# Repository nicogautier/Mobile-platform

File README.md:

# Mobile-platform

## Presentation

The mobile platform robot was developed at the [Robotics Laboratory](https://robolab.si/) of the University of Ljubljana.

The mobile platform is a robot that uses its sensors to identify and move through its environment. The final goal of the platform will be to be used in an indoor environment such as a warehouse or a retail store. It will also be combined with a collaborative manipulator robot for precise handling.

| Product | Description |
| ------ | ------ |
|[SICK nanoScan3](https://www.sick.com/hk/en/safety-laser-scanners/safety-laser-scanners/nanoscan3/nans3-caaz30an1/p/p653980?ff_data=JmZmX2lkPXA2NTM5ODAmZmZfbWFzdGVySWQ9cDY1Mzk4MCZmZl90aXRsZT1OQU5TMy1DQUFaMzBBTjEmZmZfcXVlcnk9JmZmX3Bvcz0xJmZmX29yaWdQb3M9MSZmZl9wYWdlPTEmZmZfcGFnZVNpemU9MjQmZmZfb3JpZ1BhZ2VTaXplPTI0JmZmX3NpbWk9OTcuMA==)| Laser scanners for platform protection and localization|
|[ Beckhoff CX5140 ](https://www.beckhoff.com/en-us/products/ipc/embedded-pcs/cx5100-intel-atom/cx5140.html)|Embedded PC for low-level control of sensors and actuators|

## Features

| Program | Description |
| ------ | ------ | 
|[TwinCAT](https://www.beckhoff.com/en-en/products/automation/twincat/?pk_campaign=AdWords-AdWordsSearch-TwinCAT_EN&pk_kwd=twincat&gclid=EAIaIQobChMI4qSCndXt9wIVCZBoCR0AcgaeEAAYASAAEgLjsvD_BwE)| supervises low level control of the platform (motors, joystick, laser field security, ... ) |  
|[ROS](https://www.ros.org/)| supervises high level algorithms (path-finding, SLAM algorithm, ... ) |

## How to use it

This section will explain you how to use this project.
**Note:** You will not be able to use these programs as they are if you use another robot (this one is a custom robot created in the lab), but you can of course modify or reuse part of the programs to suit them to your application.   

First you need to get the files from git:
```sh
git clone https://github.com/nicogautier/Mobile-platform && cd Mobile-platform
```

### ROS program

#### platform_communication
The **ADScommunication** node of the platform\_communication package allows to communicate with the TwinCAT program. It receives commands from the **/cmd\_vel** topic and sends them to the PLC. It also publishes the odometry on the **/odom** topic according to the values of the wheel encoders. This will allow you for example to use the ROS [navigation](https://wiki.ros.org/navigation) stack which required communication on these two subjects.

To use it in your program, you can add and compile the platform_communication package in your ROS project. Then add this line to your launch file.  

```sh
<node pkg="platform_communication" type="ADSCommunication" name="ADSCommunication"/>
```

If you want to modify this node, I recommend that you consult the [**ADS Beckhoff**](ADS&#32;Beckhoff/) folder which will explain how to use the ADS library. The two main arrays used to exchange data with the PLC are **"ControlGVL.robot\_odom "** received by ADS notification for odometry and **"ControlGVL.vel\_robot "** to send speed goals.

#### platform_main
The platform\_main package contains the main launch file and the configuration files used to implement ROS [navigation](https://wiki.ros.org/navigation) stack. It uses the [**sick\_safetyscanners**](https://wiki.ros.org/sick_safetyscanners) node to get the laserscan of the two sensors. It also uses [**TEB local planner**](https://wiki.ros.org/teb_local_planner) for the local trajectories and [**rtabmap**](http://wiki.ros.org/rtabmap_ros) for the SLAM algorithm.

#### platform_lift

The **lift_communication.py** node of the package allows to communicate with the SCU control unit through the RS232 serial [**interface**](https://medialibrary.ewellix.com/asset/16222) that manage the lift actuators . It implements a **/moveLift** action server that moves the lift to the desired position and sends a success message when reaching the final position. It also implements a **/posLift** service that returns the position of the lift.

You can add this line to your launch file to use the node. 
```sh
<node pkg="platform_lift" type="lift_communication.py" name="lift_communication"/>
```
You may have to change the port for serial communication which is currently "*/dev/ttyUSB0*" in the init_serial() function of serial_interface.py. 

#### platform_joystick

This package allows the use of a [**Logitech Extreme 3D**](https://www.logitechg.com/fr-fr/products/space/extreme-3d-pro-joystick.942-000031.html) joystick to control the mobile platform. It implements additional features compared to the joystick connected to the Beckhoff controller. You can use the **joystick.launch** file alone:

```sh
roslaunch platform_joystick joystick.launch joystickOnly:="true"
```

or in addition to the **platform_main** launchfile. Note: to enable the use of the joystick you must put the third axis down (up: ros navigation, middle: stop).

#### platform_measurements

This package was used to perform several tests: use of an external setpoint generator in TwinCAT, accuracy of the platform movements, and accuracy of the ROS navigation implementation.  

### TwinCAT program

#### Motors

The **FB_RUN_MOTOR** controls all 4 wheels for holonomic movements. It also implements the TwinCAT external setpoint generator. It can be used by both the joystick and the ROS program. The program retrieves the values from the wheel encoders to calculate the odometry and send it to ROS.

#### Sensors
The **SensorsMain** program manages the communication with the two sensors. It calculates the fields to be applied according to the current direction. It also limits the maximum speed allowed according to the fields of the sensors that are triggered. There are 8 different orientations (see next section).

#### Variables you might want to adjust

For future people who will work on the platform, here are some variables that you will probably have to adapt to your new constraints.

| Name| Type | Description |
|------|------|------|
|ControlGVL.vel_robot| LReal[3]| Velocity command sent by the ROS program.|
|ControlGVL.robot_odom|LReal[6]|Odometry send to the ROS program.|
|FB_RUN_MOTOR.ACC_MAX| LReal| Maximum acceleration allowed for the motors.|
|FB_RUN_MOTOR.VEL_WHEEL_MAX|LReal|Maximum speed allowed for the motors.|
|SensorsMain.VMAX|LReal|Maximum speed allowed for the platform when no safety field is triggered (other maximum speeds are also based on this value.)|
|SensorsMain.VTHMAX|LReal|Maximum permissible rotation speed of the platform when the first safety field is not triggered.|

### SICK sensors security
The objective was to have a safety field around the platform to stop it (cut the power safely) if there is an obstacle very close and representing a danger. 

There are also several sets of directional fields that will stop the platform (software) or reduce the maximum speed of the platform depending on the field triggered. Each set has three warning fields (18 cm, 1 m and 2.5 m). The set of fields used will be adapted according to the direction in which the platform is moving.

Each sensor is connected to the TwinCAT PLC to inform about the triggering of a field and also to the safety module of the platform which will cut the power if necessary.

You will find in the [**safety designer**](safety&#32;designer/) folder the fields used and the sensor configurations. In the [**kicad**](kicad/) folder you will find the PCB diagram used to connect the sensors to the PLC.

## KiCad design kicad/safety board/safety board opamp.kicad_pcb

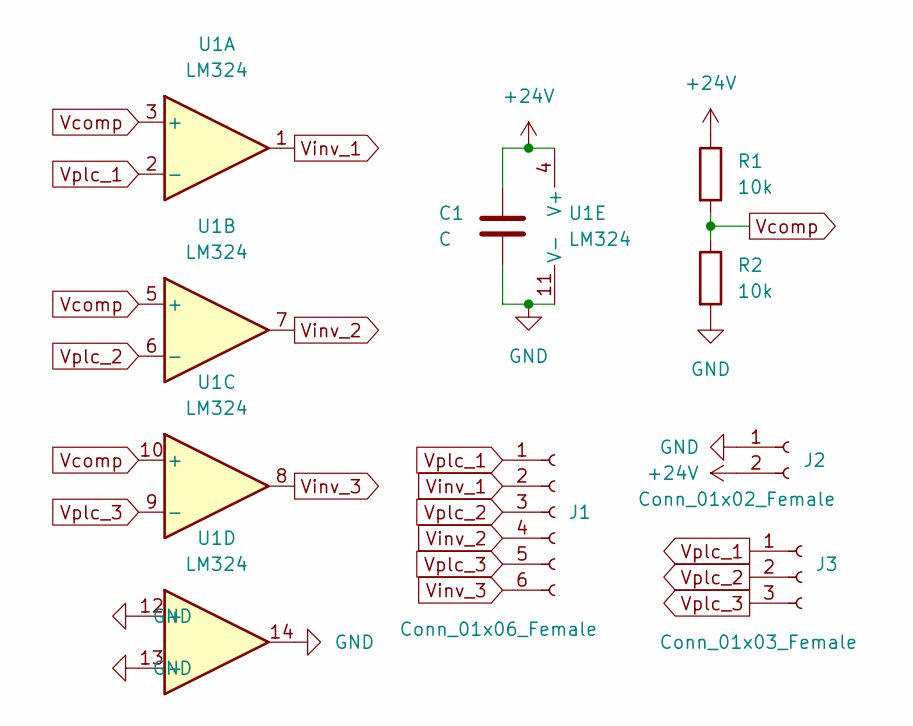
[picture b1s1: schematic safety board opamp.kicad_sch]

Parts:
C1: C
J1: Conn_01x06_Female; PinSocket_1x06_P2.54mm_Vertical
J2: Conn_01x02_Female; PinSocket_1x02_P2.54mm_Vertical
J3: Conn_01x03_Female; PinSocket_1x03_P2.54mm_Vertical
R1, R2: 10k; R_Axial_DIN0207_L6.3mm_D2.5mm_P10.16mm_Horizontal
U1: LM324; DIP-14_W7.62mm_Socket

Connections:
+24V: C1.1, J2.2, R1.1, U1.4 (V+)
GND: C1.2, J2.1, R2.2, U1.11 (V-), U1.12 (+), U1.13 (-), U1.14
Vcomp: R1.2, R2.1, U1.3 (+), U1.5 (+), U1.10 (+)
Vinv_1: J1.2, U1.1
Vinv_2: J1.4, U1.7
Vinv_3: J1.6, U1.8
Vplc_1: J1.1, J3.1, U1.2 (-)
Vplc_2: J1.3, J3.2, U1.6 (-)
Vplc_3: J1.5, J3.3, U1.9 (-)

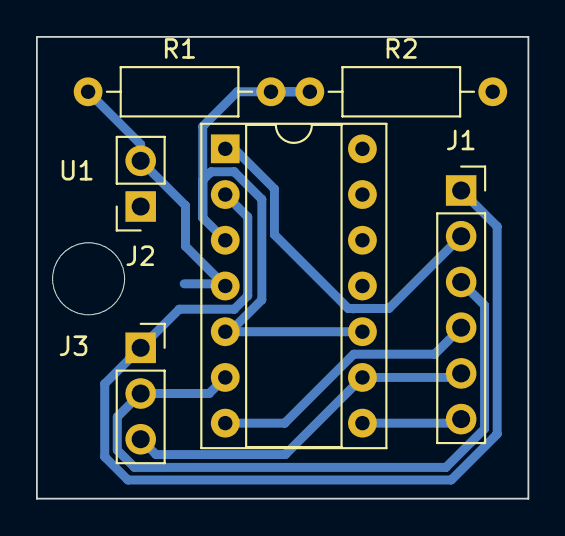
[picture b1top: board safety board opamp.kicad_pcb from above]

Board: 2 copper layers, 27.3 x 25.7 mm, 7 parts (1 on the bottom side), 9 nets.

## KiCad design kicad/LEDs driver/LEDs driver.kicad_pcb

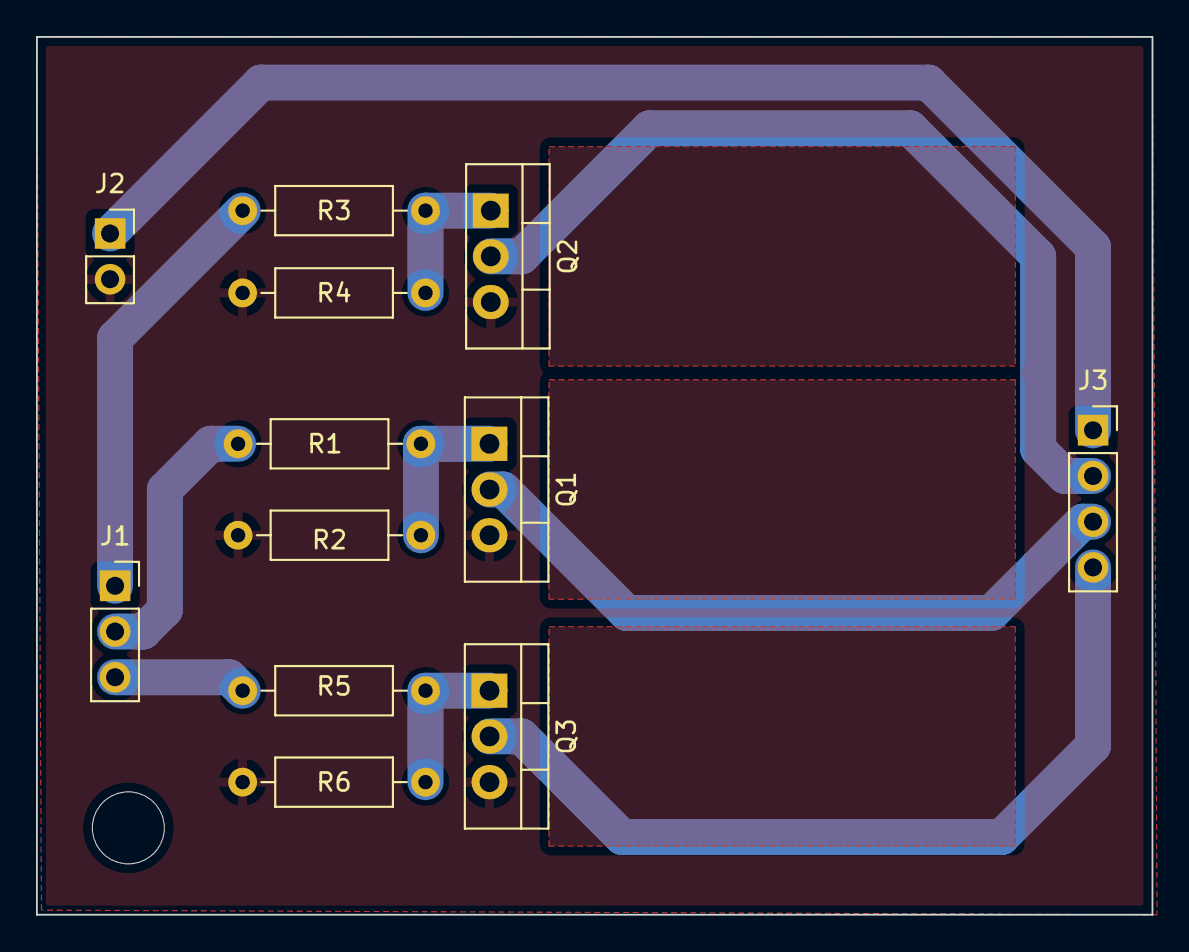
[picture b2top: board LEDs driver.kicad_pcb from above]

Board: 2 copper layers, 62.0 x 48.8 mm, 12 parts (0 on the bottom side), 11 nets.

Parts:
J1: Conn_01x03_Female; PinSocket_1x03_P2.54mm_Vertical
J2: Conn_01x02_Female; PinSocket_1x02_P2.54mm_Vertical
J3: Conn_01x04_Female; PinSocket_1x04_P2.54mm_Vertical
Q1, Q2, Q3: BUZ11; TO-220-3_Vertical
R1, R2, R3, R4, R5, R6: R; R_Axial_DIN0207_L6.3mm_D2.5mm_P10.16mm_Horizontal

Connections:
+12V: J2.1, J3.1
Bin: J1.3, R5.1
Bout: J3.4, Q3.2 (D)
GND: J2.2, Q1.3 (S), Q2.3 (S), Q3.3 (S), R2.2, R4.2, R6.2
Gin: J1.1, R3.1
Gout: J3.2, Q2.2 (D)
unnamed: Q1.1 (G), R1.2, R2.1
unnamed: Q2.1 (G), R3.2, R4.1
unnamed: Q3.1 (G), R5.2, R6.1
Rin: J1.2, R1.1
Rout: J3.3, Q1.2 (D)

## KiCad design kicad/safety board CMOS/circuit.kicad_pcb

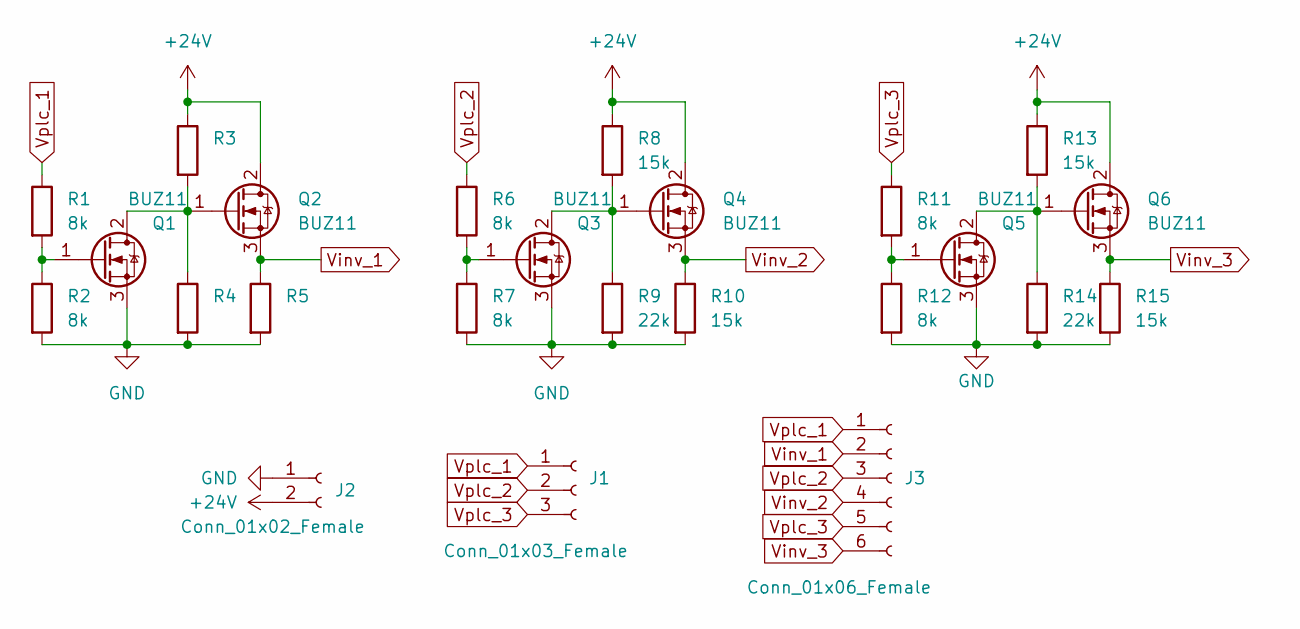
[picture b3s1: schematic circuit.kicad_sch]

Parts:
J1: Conn_01x03_Female; PinSocket_1x03_P2.54mm_Vertical
J2: Conn_01x02_Female; PinSocket_1x02_P2.54mm_Vertical
J3: Conn_01x06_Female; PinSocket_1x06_P2.54mm_Vertical
Q1, Q2, Q3, Q4, Q5, Q6: BUZ11; TO-220-3_Vertical
R1, R2, R6, R7, R11, R12: 8k; R_Axial_DIN0207_L6.3mm_D2.5mm_P10.16mm_Horizontal
R3, R4, R5: R_Axial_DIN0207_L6.3mm_D2.5mm_P10.16mm_Horizontal
R8, R10, R13, R15: 15k; R_Axial_DIN0207_L6.3mm_D2.5mm_P10.16mm_Horizontal
R9, R14: 22k; R_Axial_DIN0207_L6.3mm_D2.5mm_P10.16mm_Horizontal

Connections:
+24V: J2.2, Q2.2 (D), Q4.2 (D), Q6.2 (D), R3.1, R8.1, R13.1
GND: J2.1, Q1.3 (S), Q3.3 (S), Q5.3 (S), R2.2, R4.2, R5.2, R7.2, R9.2, R10.2, R12.2, R14.2, R15.2
unnamed: Q1.1 (G), R1.2, R2.1
unnamed: Q1.2 (D), Q2.1 (G), R3.2, R4.1
unnamed: Q3.1 (G), R6.2, R7.1
unnamed: Q3.2 (D), Q4.1 (G), R8.2, R9.1
unnamed: Q5.1 (G), R11.2, R12.1
unnamed: Q5.2 (D), Q6.1 (G), R13.2, R14.1
Vinv_1: J3.2, Q2.3 (S), R5.1
Vinv_2: J3.4, Q4.3 (S), R10.1
Vinv_3: J3.6, Q6.3 (S), R15.1
Vplc_1: J1.1, J3.1, R1.1
Vplc_2: J1.2, J3.3, R6.1
Vplc_3: J1.3, J3.5, R11.1

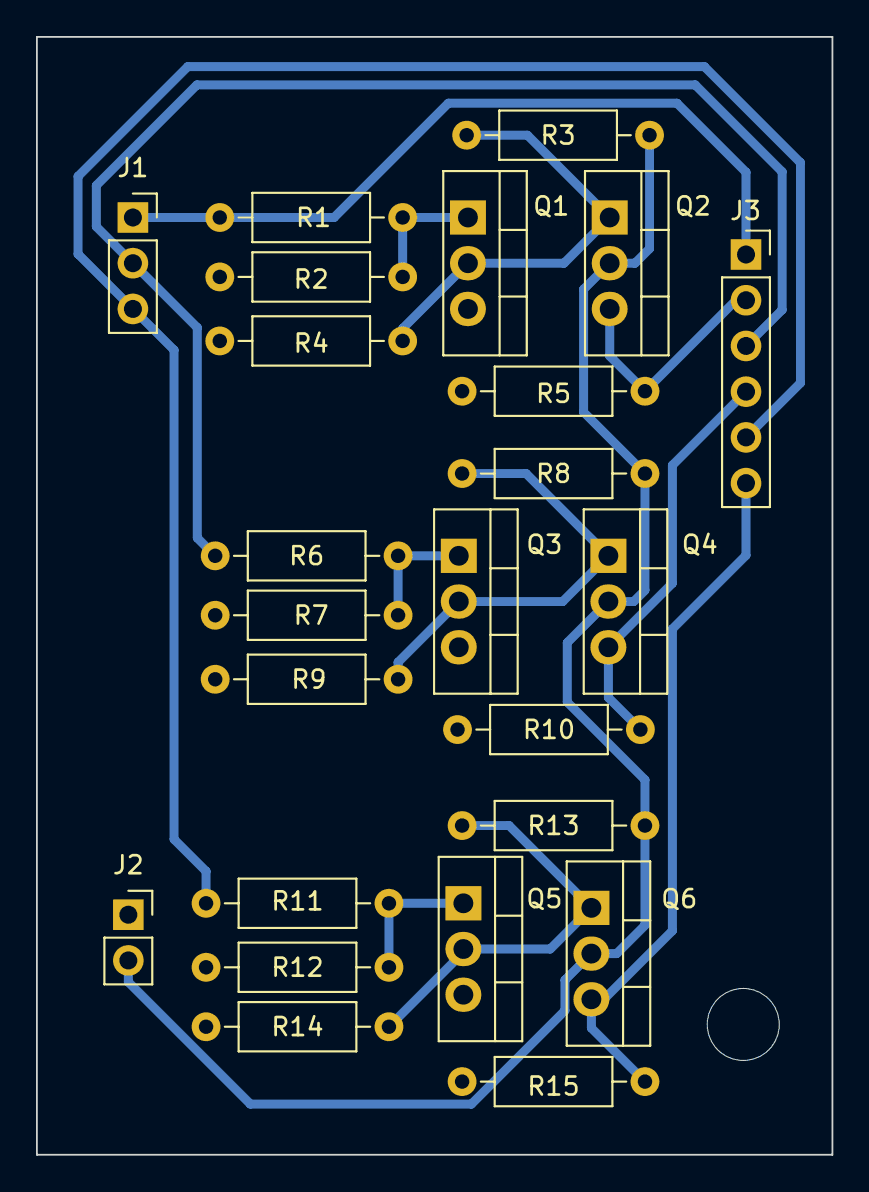
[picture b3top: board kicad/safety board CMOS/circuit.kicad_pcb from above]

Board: 2 copper layers, 44.2 x 62.1 mm, 24 parts (0 on the bottom side), 14 nets.

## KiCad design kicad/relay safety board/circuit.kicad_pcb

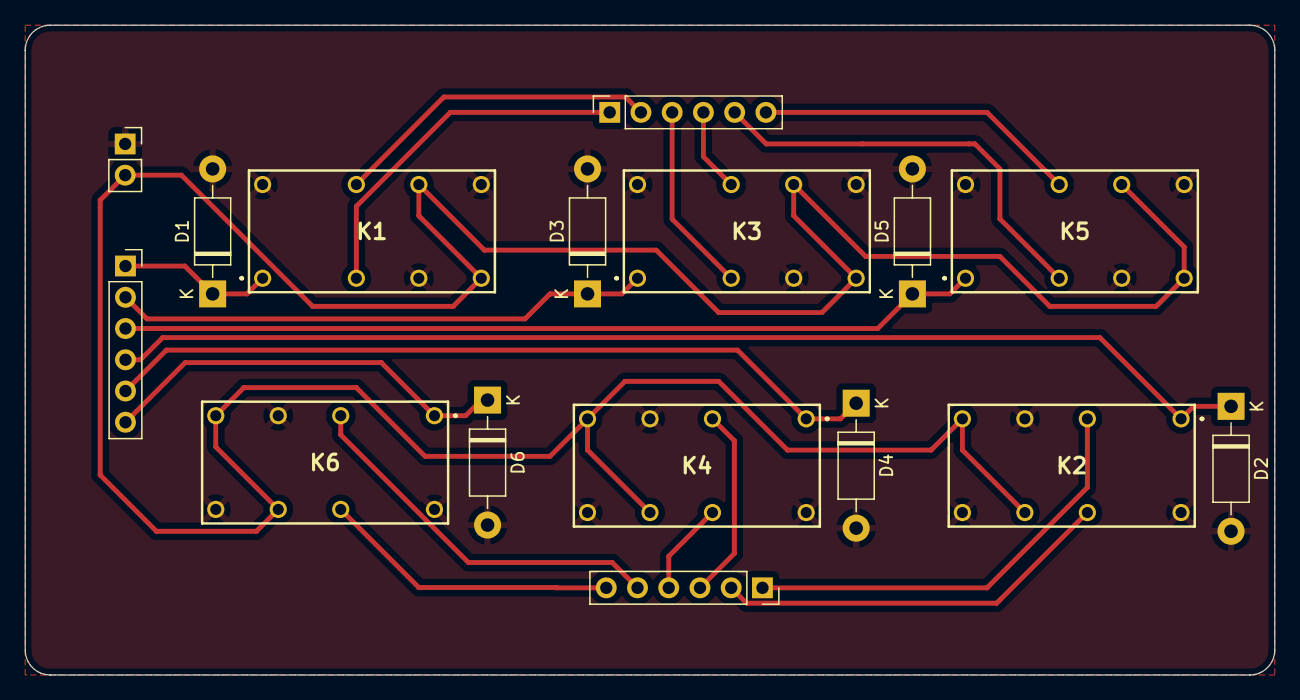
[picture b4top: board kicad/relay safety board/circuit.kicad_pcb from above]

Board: 2 copper layers, 101.6 x 52.8 mm, 16 parts (0 on the bottom side), 20 nets.

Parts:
 : PinSocket_1x06_P2.54mm_Vertical
 #2: PinSocket_1x02_P2.54mm_Vertical
 #3,  #4: PinSocket_1x06_P2.54mm_Vertical
D1, D2, D3, D4, D5, D6: 1N4001; D_DO-41_SOD81_P10.16mm_Horizontal
K1, K2, K3, K4, K5, K6: DS2Y-S-DC24V

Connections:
+24V: #2.2, K1.8 (NO_1), K1.11 (NC_2), K2.8 (NO_1), K2.11 (NC_2), K3.8 (NO_1), K3.11 (NC_2), K4.8 (NO_1), K4.11 (NC_2), K5.8 (NO_1), K5.11 (NC_2), K6.8 (NO_1), K6.11 (NC_2)
GND: #2.1, D1.2 (A), D2.2 (A), D3.2 (A), D4.2 (A), D5.2 (A), D6.2 (A), K1.6 (NC_1), K1.9 (NO_2), K1.16 (COIL-), K2.6 (NC_1), K2.9 (NO_2), K2.16 (COIL-), K3.6 (NC_1), K3.9 (NO_2), K3.16 (COIL-), K4.6 (NC_1), K4.9 (NO_2), K4.16 (COIL-), K5.6 (NC_1), K5.9 (NO_2), K5.16 (COIL-), K6.6 (NC_1), K6.9 (NO_2), K6.16 (COIL-)
S1_11: #3.1, K1.4 (COM_1)
S1_12: #3.2, K1.13 (COM_2)
S1_13: #3.3, K3.4 (COM_1)
S1_14: #3.4, K3.13 (COM_2)
S1_15: #3.5, K5.4 (COM_1)
S1_16: #3.6, K5.13 (COM_2)
S1_D: #4.1, D1.1 (K), K1.1 (COIL+)
S1_E: #4.2, D3.1 (K), K3.1 (COIL+)
S1_F: #4.3, D5.1 (K), K5.1 (COIL+)
S2_11: .1, K2.4 (COM_1)
S2_12: .2, K2.13 (COM_2)
S2_13: .3, K4.4 (COM_1)
S2_14: .4, K4.13 (COM_2)
S2_15: .5, K6.4 (COM_1)
S2_16: .6, K6.13 (COM_2)
S2_D: #4.4, D2.1 (K), K2.1 (COIL+)
S2_E: #4.5, D4.1 (K), K4.1 (COIL+)
S2_F: #4.6, D6.1 (K), K6.1 (COIL+)

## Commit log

2022-05-11 initialise git repository
2022-05-11 init: add files
2022-05-12 ROS: measurements node to perform navigation tests with Optotrak cameras
2022-05-12 change commands of trajectories for measurements
2022-05-12 fixed strange rotations when moving
2022-05-13 adjust some local planner parameters to improve trajectory but still some weird movements when moving sideways (rotate)
2022-05-16 python scripts to transfert odometry position from ROS to simulink
2022-05-16 simulink project to compare odometry and optotrack
2022-05-17 simulink experiments
2022-05-17 reorder files
2022-05-17 remove unused folder
2022-05-17 analyse expertiments data
2022-05-18 simulink analyse all
2022-05-19 fix transform UDP
2022-05-19 restructure ROS project
2022-05-20 simulink scripts analyse datas
2022-05-20 update README ROS
2022-05-20 fields img
2022-05-23 fix theta tf measurements
2022-05-24 update simulink analyse
2022-05-25 improve navigation but stilla bit of jerk
2022-05-25 still improve navigation trajectory smoother
2022-05-25 twincat: add delay before updating sensors
2022-05-26 simulink: add figure analyse all
2022-05-26 ROS: implementation joystick
2022-05-26 ROS: switch between joystick/autonomous
2022-05-26 ROS: fix switch mode joystick/navigation
2022-05-26 ROS: joystick add third mode stop
2022-05-26 no more jerk during navigation
2022-05-27 remove joystick service to ros parameter/ enable joystick use only
2022-05-27 ros: adjust navigation slowest movements
2022-05-27 READ.ME twincat variables
2022-05-27 twincat: update variables
2022-05-27 twincat: update variable
2022-05-27 ros: small adjustements
2022-06-03 serial RS232 lift
2022-06-06 send and receive serial
2022-06-06 serial: receive pos
2022-06-07 serial: restructure program
2022-06-07 serial: move lift but issue only one order
2022-06-07 serial: move the lift
2022-06-08 serial: fixed can't used full range ofl range
2022-06-08 serial: create interface
2022-06-08 serial: used semaphore to enable ros multithread
2022-06-08 serial: start creating action server
2022-06-09 lift: actionServer MoveLift
2022-06-09 lift: clean python files
2022-06-09 lift: ros service to get position
2022-06-10 clean repository
2022-06-10 add .gitignore
2022-06-15 safety board V2: CMOS
2022-06-15 increase size global costmap
2022-06-23 LEDs driver + new CMOS safety PCB
2022-06-30 new safety board
2022-06-30 remove useless kicad files
